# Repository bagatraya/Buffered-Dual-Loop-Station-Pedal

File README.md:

# Buffered-Dual-Loop-Station-Pedal
A project showcasing the design and development of a Buffered Dual Loop Station Effect Pedal, using the TL074 op-amp for low-noise buffering and inverting circuits. This repository includes the schematic, PCB design, simulation files, and a detailed project report.

## Features  
- **Buffered Input and Outputs**: Maintains signal integrity with low-noise TL074 op-amps.  
- **Phase Inversion**: Switchable inverting circuit for phase adjustment on Return 1.  
- **Signal Blending**: Blend potentiometer to control the balance between two return signals.  
- **Live-Tested**: Successfully used in live performance settings.  

## Repository Contents  
- **Hardware**: Schematic, PCB designs, and Bill of Materials (BOM).  
- **Simulations**: Proteus simulation files and results.  
- **Photos and Demos**: Images and video of the build and live testing.

## Simulation

## PCB Circuit

## PCB Design

## Final Result

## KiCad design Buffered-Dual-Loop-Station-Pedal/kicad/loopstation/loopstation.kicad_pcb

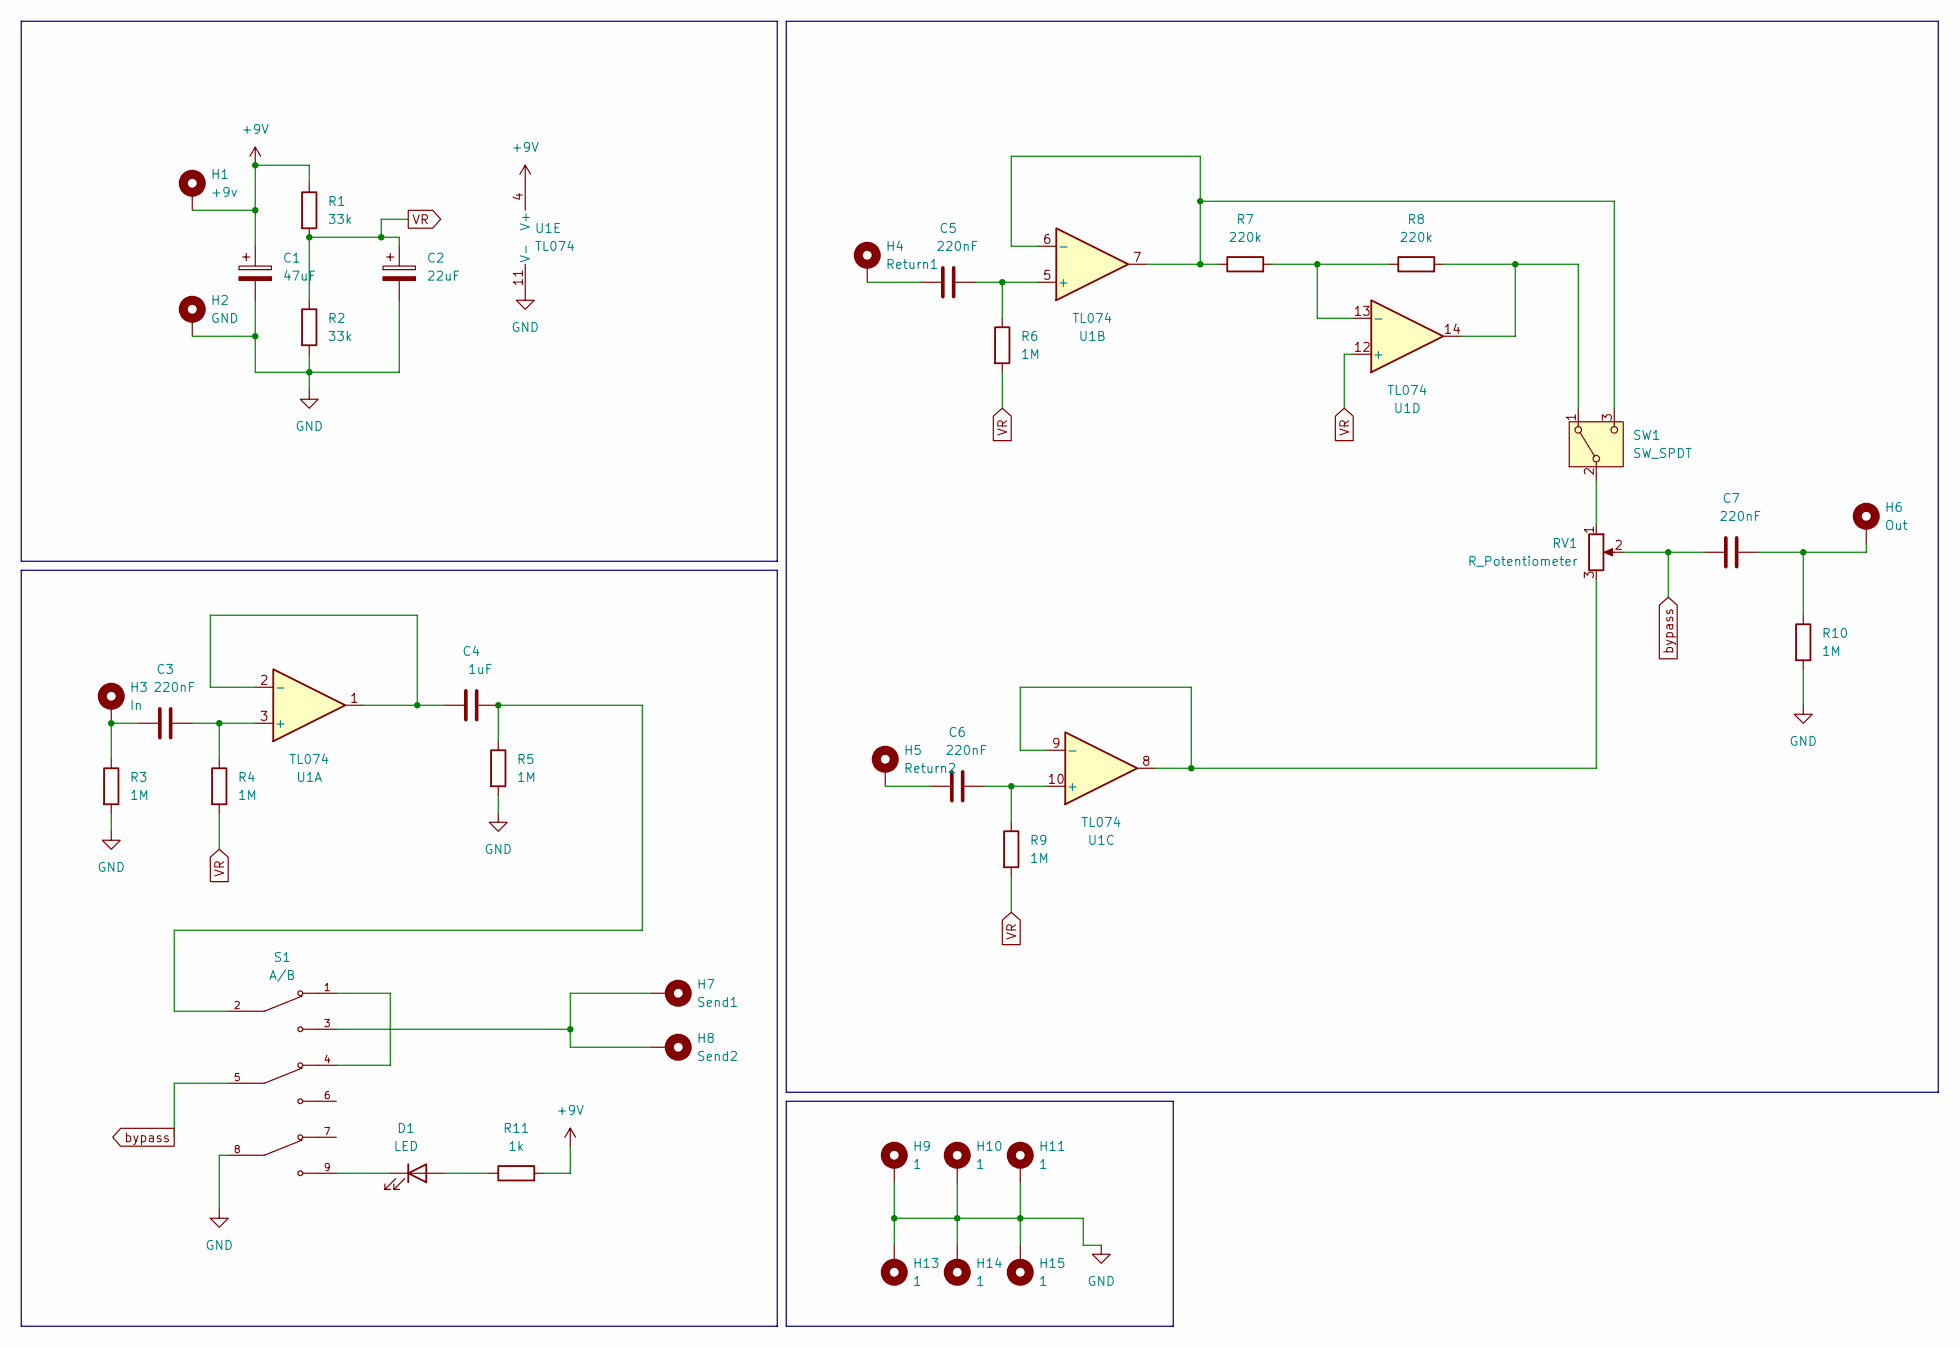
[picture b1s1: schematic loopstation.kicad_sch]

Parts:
C1: 47uF; CP_Radial_D8.0mm_P5.00mm
C2: 22uF; CP_Radial_D8.0mm_P5.00mm
C3, C5, C6, C7: 220nF; C_Rect_L7.0mm_W2.5mm_P5.00mm
C4: 1uF; C_Rect_L7.0mm_W2.5mm_P5.00mm
D1: LED; LED_D5.0mm
H1: +9v; MountingHole_2.2mm_M2_DIN965_Pad
H2: GND; MountingHole_2.2mm_M2_DIN965_Pad
H3: In; MountingHole_2.2mm_M2_DIN965_Pad
H4: Return1; MountingHole_2.2mm_M2_DIN965_Pad
H5: Return2; MountingHole_2.2mm_M2_DIN965_Pad
H6: Out; MountingHole_2.2mm_M2_DIN965_Pad
H7: Send1; MountingHole_2.2mm_M2_DIN965_Pad
H8: Send2; MountingHole_2.2mm_M2_DIN965_Pad
H9, H10, H11, H13, H14, H15: 1; MountingHole_2.2mm_M2_DIN965_Pad
R1, R2: 33k; R_Axial_DIN0207_L6.3mm_D2.5mm_P7.62mm_Horizontal
R3, R4, R5, R6, R9, R10: 1M; R_Axial_DIN0207_L6.3mm_D2.5mm_P7.62mm_Horizontal
R7, R8: 220k; R_Axial_DIN0207_L6.3mm_D2.5mm_P7.62mm_Horizontal
R11: 1k; R_Axial_DIN0207_L6.3mm_D2.5mm_P7.62mm_Horizontal
RV1: R_Potentiometer; Potentiometer_Alps_RK163_Single_verticalback
S1: A/B; SW_FS57003PLT2B2M2QE; PARTREV 4.2.2018
SW1: SW_SPDT; SPDT
U1: TL074; DIP-14_W7.62mm

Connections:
+9V: C1.1, H1.1, R1.1, R11.2, U1.4 (V+)
GND: C1.2, C2.2, H2.1, H9.1, H10.1, H11.1, H13.1, H14.1, H15.1, R2.2, R3.2, R5.2, R10.2, S1.8, U1.11 (V-)
unnamed: C3.1, H3.1, R3.1
unnamed: C4.2, R5.1, S1.2
unnamed: C5.1, H4.1
unnamed: C6.1, H5.1
unnamed: C7.2, H6.1, R10.1
unnamed: D1.2 (A), R11.1
unnamed: D1.1 (K), S1.9
unnamed: H7.1, H8.1, S1.3
unnamed: S1.1, S1.4
unnamed: R8.2, SW1.1 (A), U1.14
unnamed: RV1.1, SW1.2 (B)
unnamed: R7.1, SW1.3 (C), U1.6 (-), U1.7
unnamed: C3.2, R4.1, U1.3 (+)
unnamed: C4.1, U1.1, U1.2 (-)
unnamed: C5.2, R6.1, U1.5 (+)
unnamed: C6.2, R9.1, U1.10 (+)
unnamed: RV1.3, U1.8, U1.9 (-)
unnamed: R7.2, R8.1, U1.13 (-)
VR: C2.1, R1.2, R2.1, R4.2, R6.2, R9.2, U1.12 (+)
bypass: C7.1, RV1.2, S1.5

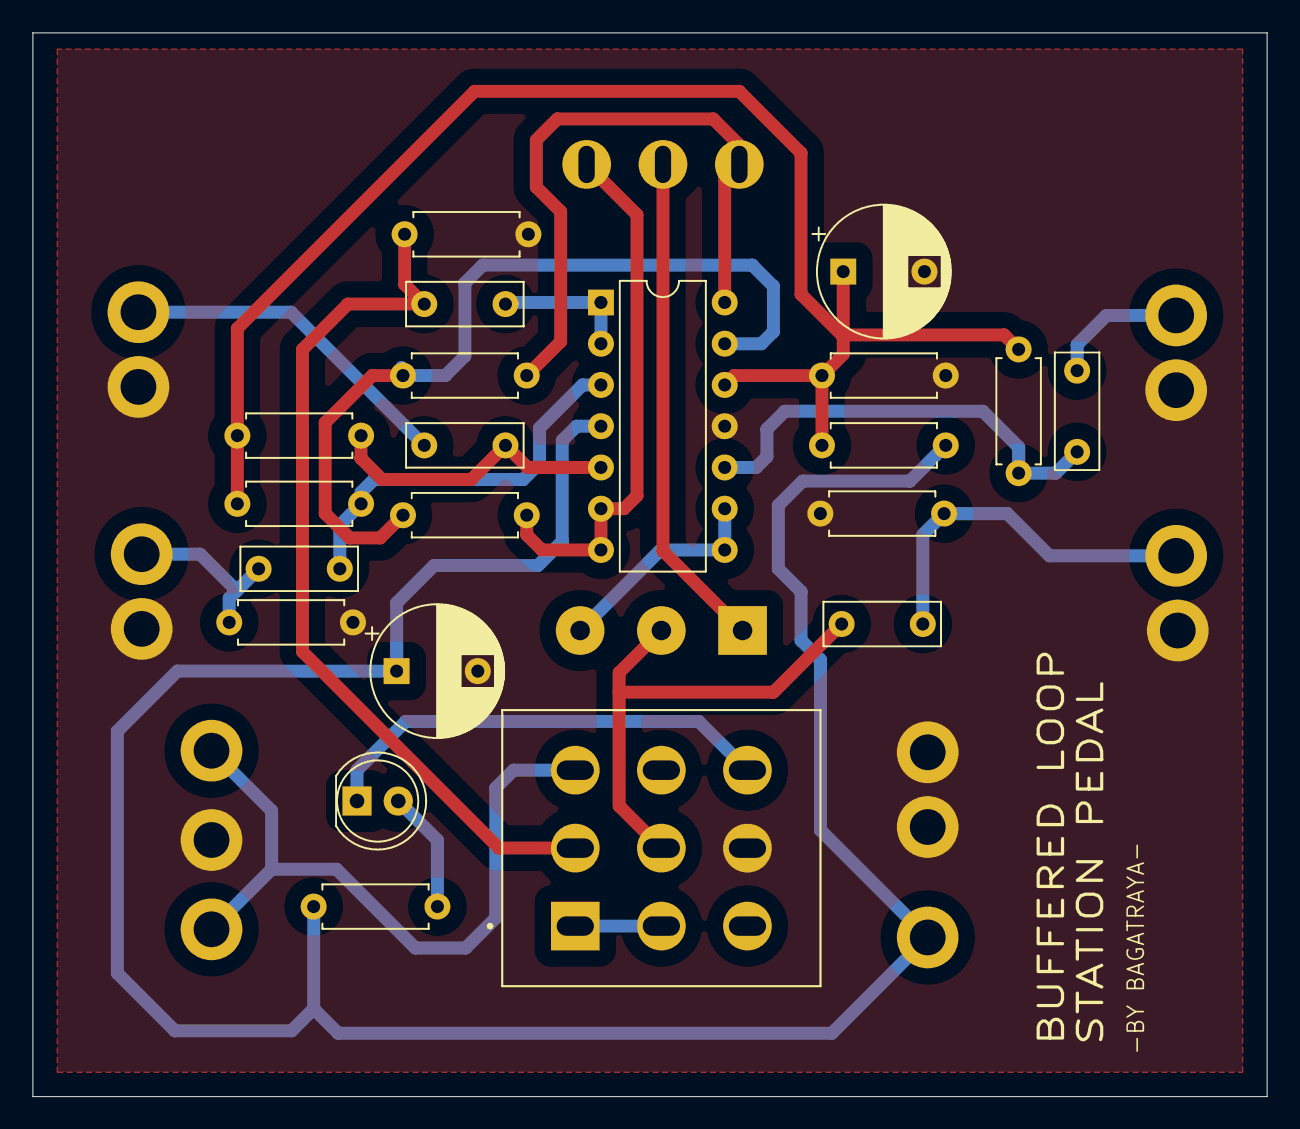
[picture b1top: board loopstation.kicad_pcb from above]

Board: 2 copper layers, 76.0 x 65.5 mm, 37 parts (1 on the bottom side), 22 nets.

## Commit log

2024-11-20 Create Buffered-Dual-Loop-Station-Pedal
